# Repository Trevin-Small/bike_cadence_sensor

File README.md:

# bike_cadence_sensor
 DIY Cadence Sensor for a Bike, built off an nrf52810 module (Ezurio BL651 453-0005)

Uses a gyroscope to measure rotational velocity, and ANT+ to communicate data to a fitness watch.

Custom PCB, Zephyr RTOS, ANT+ Communication

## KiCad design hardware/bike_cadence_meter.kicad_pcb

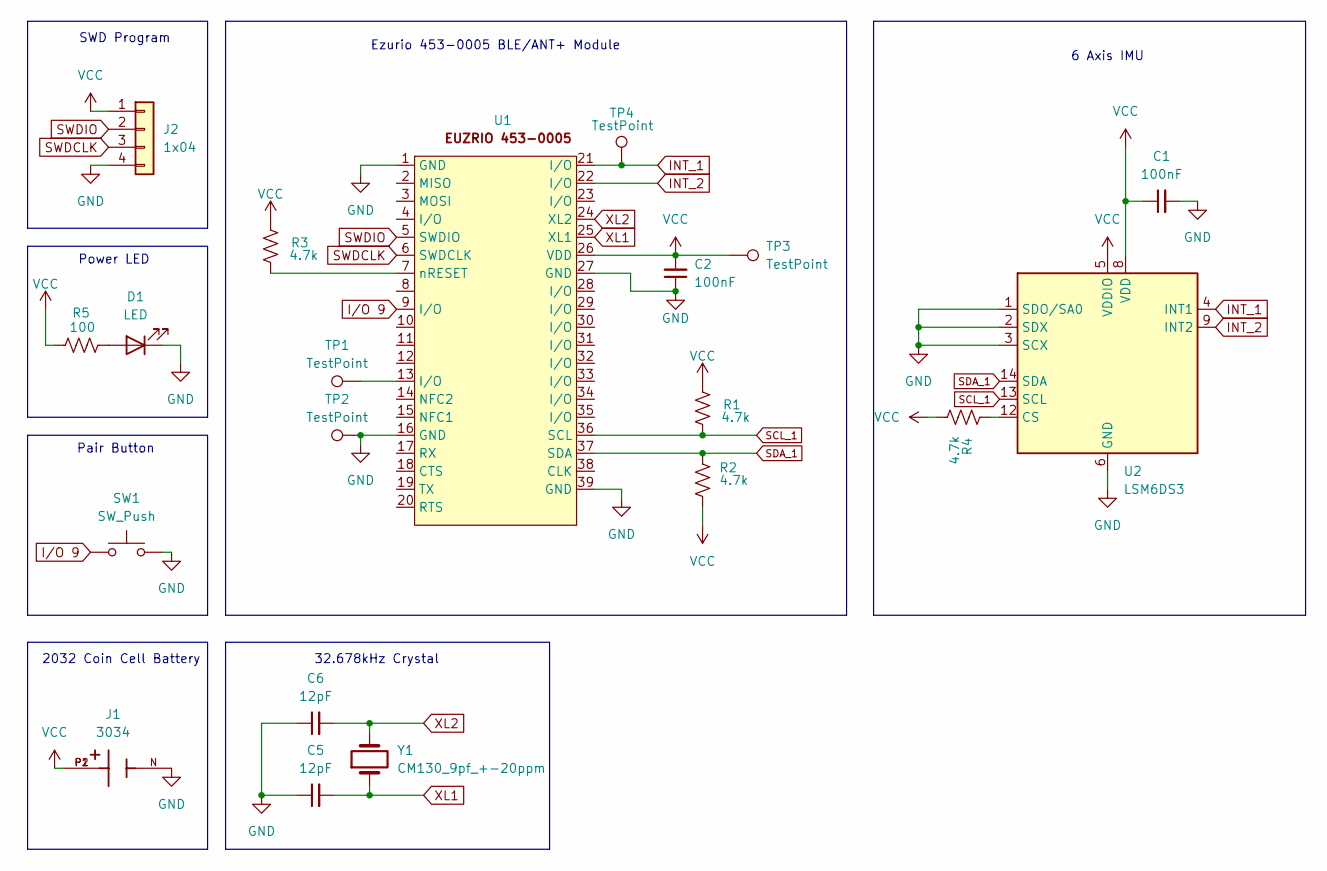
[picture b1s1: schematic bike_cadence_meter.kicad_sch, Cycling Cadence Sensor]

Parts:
C1, C2: 100nF; C_0603_1608Metric
C5, C6: 12pF; C_0603_1608Metric
D1: LED; LED_0603_1608Metric
J1: 3034; BAT_3034; PARTREV G
J2: 1x04; PinHeader_1x04_P2.54mm_Vertical
R1, R2, R4: 4.7k; R_0603_1608Metric
R3: 4.7k; R_0603_1608Metric; LCSC C23162
R5: 100; R_0603_1608Metric
SW1: SW_Push; SW_Push_1P1T_XKB_TS-1187A
TP1, TP2, TP3, TP4: TestPoint; TestPoint_Pad_D1.0mm
U1: Euzrio 453-00005
U2: LSM6DS3; LGA-14_3x2.5mm_P0.5mm_LayoutBorder3x4y
Y1: CM130_9pf_+-20ppm; CM130 32.768 DZCT

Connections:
GND: C1.2, C2.1, C5.1, C6.1, D1.1 (K), J1.N, J2.4, SW1.2, TP2.1, U1.1 (GND), U1.16 (GND), U1.27 (GND), U1.39 (GND), U2.1 (SDO/SA0), U2.2 (SDX), U2.3 (SCX), U2.6 (GND), U2.7 (GND)
INT_1: TP4.1, U1.21 (I/O), U2.4 (INT1)
INT_2: U1.22 (I/O), U2.9 (INT2)
I/O 9: SW1.1, U1.9 (I/O)
unnamed: D1.2 (A), R5.2
unnamed: TP1.1, U1.13 (I/O)
unnamed: R3.2, U1.7 (nRESET)
unnamed: R4.1, U2.12 (CS)
SCL_1: R1.2, U1.36 (SCL), U2.13 (SCL)
SDA_1: R2.1, U1.37 (SDA), U2.14 (SDA)
SWDCLK: J2.3, U1.6 (SWDCLK)
SWDIO: J2.2, U1.5 (SWDIO)
VCC: C1.1, C2.2, J1.P1, J1.P2, J2.1, R1.1, R2.2, R3.1, R4.2, R5.1, TP3.1, U1.26 (VDD), U2.5 (VDDIO), U2.8 (VDD)
XL1: C5.2, U1.25 (XL1), Y1.1
XL2: C6.2, U1.24 (XL2), Y1.2

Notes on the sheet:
32.678kHz Crystal
Power LED
6 Axis IMU
Ezurio 453-0005 BLE/ANT+ Module
2032 Coin Cell Battery
Pair Button
SWD Program

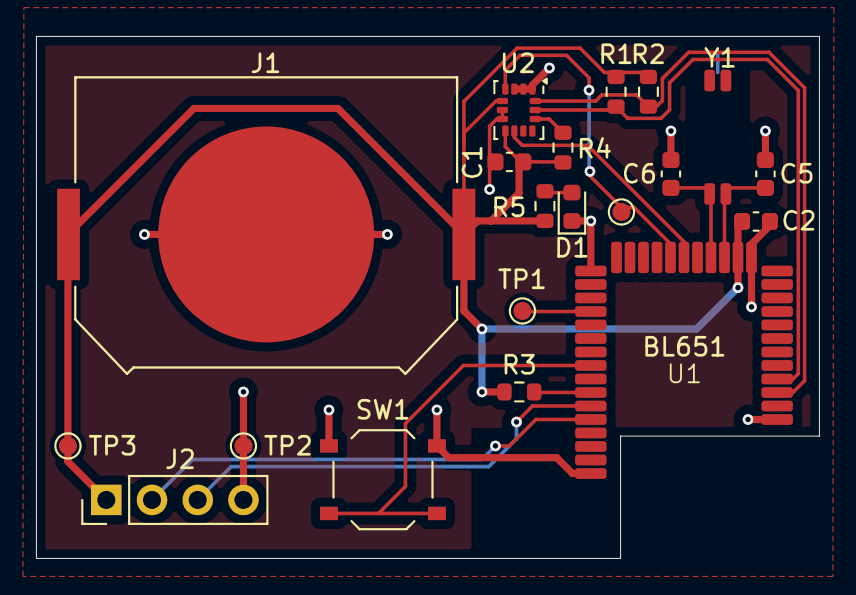
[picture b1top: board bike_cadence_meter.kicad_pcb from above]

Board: 2 copper layers, 43.5 x 29.0 mm, 20 parts (0 on the bottom side), 15 nets.

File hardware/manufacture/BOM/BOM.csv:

Reference,Value,Footprint,Qty,DNP,JLPCB Part #
"C1,C2",100nF,Capacitor_SMD:C_0603_1608Metric,2,, C14663
"C5,C6",12pF,Capacitor_SMD:C_0603_1608Metric,2,, C38523
D1,LED,LED_SMD:LED_0603_1608Metric,1,,C2286
J1,3034,Coin_cell_batt:BAT_3034,1,Y,
J2,1x04,Connector_PinHeader_2.54mm:PinHeader_1x04_P2.54mm_Vertical,1,Y,
"R1,R2,R3,R4",4.7k,Resistor_SMD:R_0603_1608Metric,4,, C23162
R5,100,Resistor_SMD:R_0603_1608Metric,1,, C22775
SW1,SW_Push,Button_Switch_SMD:SW_Push_1P1T_XKB_TS-1187A,1,, C318884
U1,~,Custom Components:Euzrio 453-00005,1,Y,
U2,LSM6DS3,Package_LGA:LGA-14_3x2.5mm_P0.5mm_LayoutBorder3x4y,1,, C967633
Y1,CM130_9pf_+-20ppm,32.768khz crystal:CM130 32.768 DZCT,1,Y,

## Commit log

2024-06-18 Added custom footprint/symbol/models
2024-06-18 remove duplicate
2024-06-18 Remove unnecessary files
2024-06-18 Add pcb render, bl651 model
2024-06-18 update model in pcb
2024-06-25 Add manufacturing files
2024-07-24 Fixed reversed LED
